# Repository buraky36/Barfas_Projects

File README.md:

# Barfas_Projects
IoT and Access Controller Projects

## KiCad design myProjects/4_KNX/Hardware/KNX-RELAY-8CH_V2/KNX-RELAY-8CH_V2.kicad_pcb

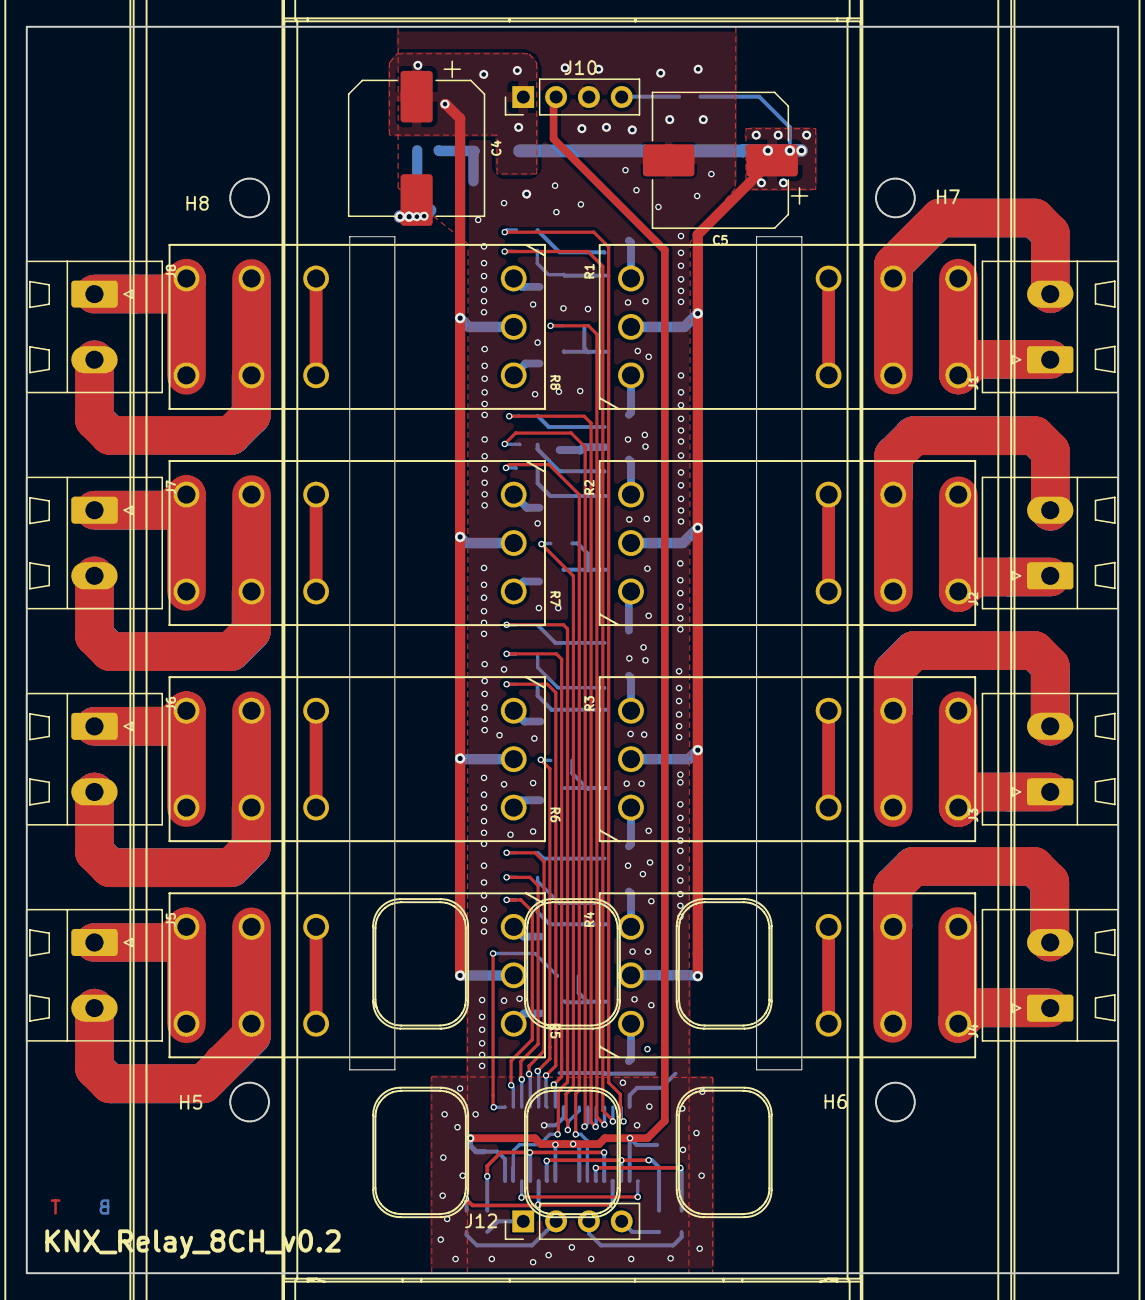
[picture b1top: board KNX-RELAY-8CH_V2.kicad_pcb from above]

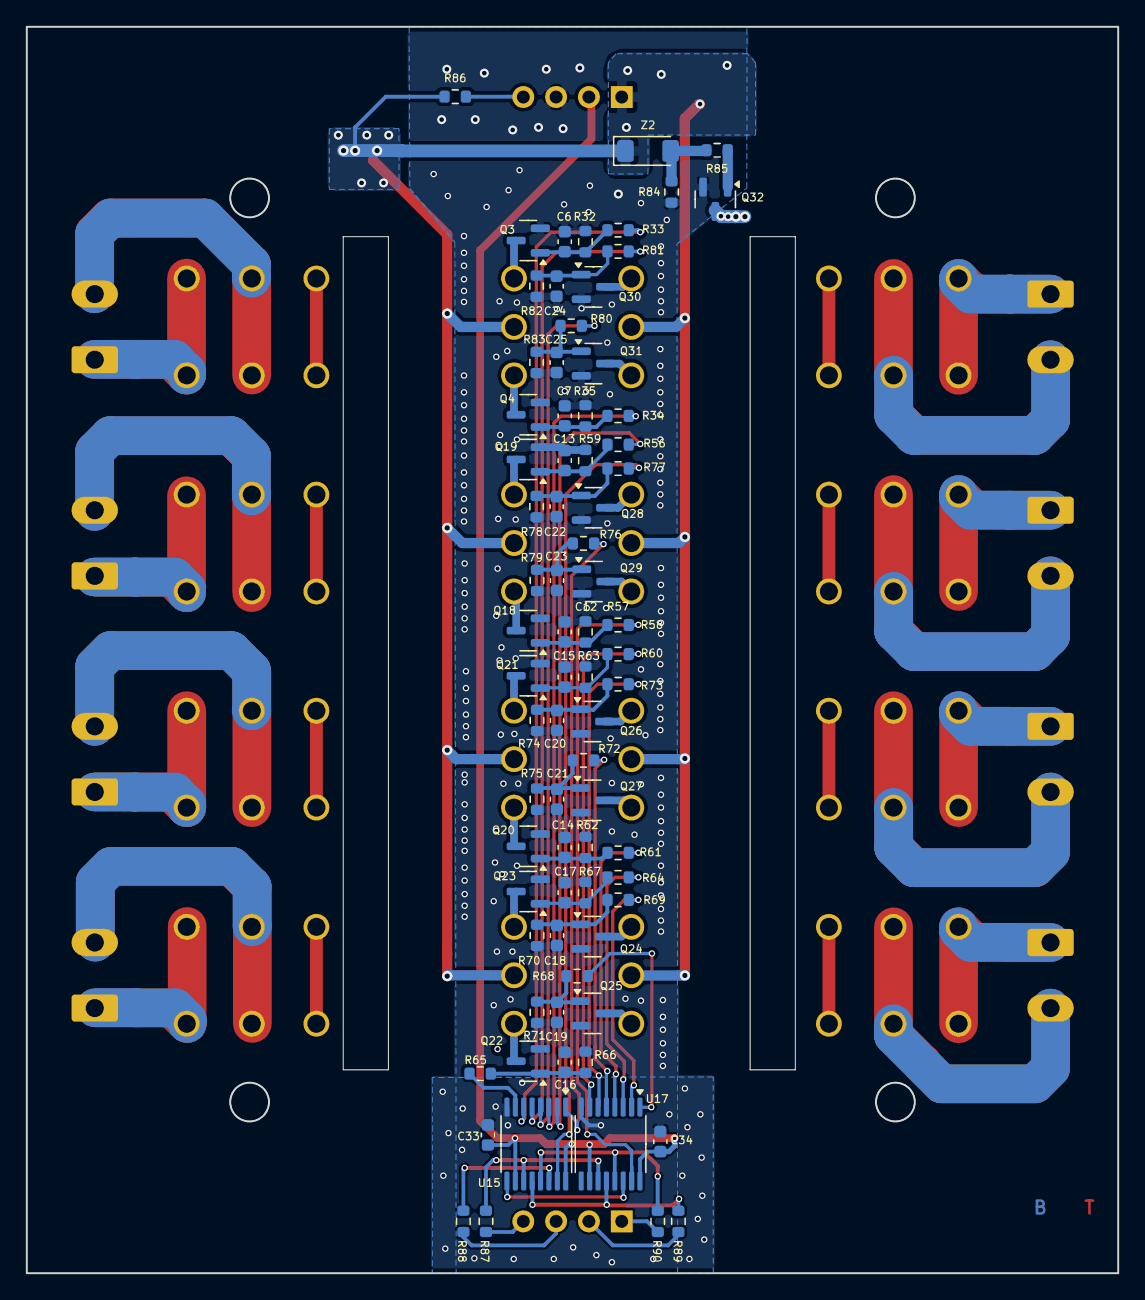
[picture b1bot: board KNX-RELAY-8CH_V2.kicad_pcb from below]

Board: 2 copper layers, 84.5 x 96.5 mm, 101 parts (77 on the bottom side), 80 nets.

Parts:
C4, C5: 1000uf/16V; CP_Elec_10x10
C6, C7, C12, C13, C14, C15, C16, C17, C18, C19, C20, C21, C22, C23, C24, C25: 100nF; C_0603_1608Metric
C33, C34: 100nF/50V; C_0603_1608Metric
H5, H6, H7, H8: MountingHole; MountingHole_3mm
J1, J2, J3, J4, J5, J6, J7, J8: DG129-5.08-02P-14-00AH; DG129-5.08-02P
J10, J12: Conn_01x04; PinHeader_1x04_P2.54mm_Vertical
Q3, Q4, Q18, Q19, Q20, Q21, Q22, Q23, Q24, Q25, Q26, Q27, Q28, Q29, Q30, Q31, Q32: 2N7002ET1G; SOT-23
R1, R2, R3, R4, R5, R6, R7, R8: RT314F12; RELAY9-500X1142_618
R32, R35, R58, R59, R62, R63, R66, R67, R70, R71, R74, R75, R78, R79, R82, R83, R84, R85: 10K; R_0603_1608Metric
R33, R34, R56, R57, R60, R61, R64, R65, R68, R69, R72, R73, R76, R77, R80, R81: 1K; R_0603_1608Metric
R86: 0R; R_0603_1608Metric
R87, R88, R89, R90: 33R; R_0603_1608Metric
U15, U17: 74HC595PW,118; TSSOP-16_4.4x5mm_P0.65mm
Z2: 6.8V; D_MiniMELF

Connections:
+3V3: C33.2, C34.2, J10.2, U15.10 (~SRCLR), U15.16 (VCC), U17.10 (~SRCLR), U17.16 (VCC)
+12V: C4.1, C5.1, J10.1, R1.A3, R2.A3, R3.A3, R4.A3, R5.A3, R6.A3, R7.A3, R8.A3, R86.1, Z2.1 (K)
/RELAYS/R1_COM: J1.2, R1.11
/RELAYS/R1_NO: J1.1, R1.14
/RELAYS/R2_COM: J2.2, R2.11
/RELAYS/R2_NO: J2.1, R2.14
/RELAYS/R3_COM: J3.2, R3.11
/RELAYS/R3_NO: J3.1, R3.14
/RELAYS/R4_COM: J4.2, R4.11
/RELAYS/R4_NO: J4.1, R4.14
/RELAYS/R5_COM: J5.2, R5.11
/RELAYS/R5_NO: J5.1, R5.14
/RELAYS/R6_COM: J6.2, R6.11
/RELAYS/R6_NO: J6.1, R6.14
/RELAYS/R7_COM: J7.2, R7.11
/RELAYS/R7_NO: J7.1, R7.14
/RELAYS/R8_COM: J8.2, R8.11
/RELAYS/R8_NO: J8.1, R8.14
/Shift register/ShiftRegCLK: R87.2, U15.11 (SRCLK), U17.11 (SRCLK)
/Shift register/ShiftRegDATA: R88.2, U15.14 (SER)
/Shift register/ShiftReg_Latch: R89.2, U15.12 (RCLK), U17.12 (RCLK)
/Shift register/Shift_~OE: R90.2, U15.13 (~OE), U17.13 (~OE)
GNDD: C5.2, C6.1, C7.1, C12.1, C13.1, C14.1, C15.1, C16.1, C17.1, C18.1, C19.1, C20.1, C21.1, C22.1, C23.1, C24.1, C25.1, C33.1, C34.1, J10.3, Q3.2 (S), Q4.2 (S), Q18.2 (S), Q19.2 (S), Q20.2 (S), Q21.2 (S), Q22.2 (S), Q23.2 (S), Q24.2 (S), Q25.2 (S), Q26.2 (S), Q27.2 (S), Q28.2 (S), Q29.2 (S), Q30.2 (S), Q31.2 (S), Q32.2 (S), R32.1, R35.1, R58.1, R59.1, R62.1, R63.1, R66.1, R67.1, R70.1, R71.1, R74.1, R75.1, R78.1, R79.1, R82.1, R83.1, R84.1, U15.8 (GND), U17.8 (GND)
unnamed: J12.1, R90.1
unnamed: J12.2, R89.1
unnamed: J12.3, R88.1
unnamed: J12.4, R87.1
unnamed: Q3.3 (D), R1.A2
unnamed: C6.2, Q3.1 (G), R32.2, R33.1
unnamed: Q4.3 (D), R1.A1
unnamed: C7.2, Q4.1 (G), R34.1, R35.2
unnamed: Q18.3 (D), R2.A1
unnamed: C12.2, Q18.1 (G), R57.1, R58.2
unnamed: Q19.3 (D), R2.A2
unnamed: C13.2, Q19.1 (G), R56.1, R59.2
unnamed: Q20.3 (D), R3.A1
unnamed: C14.2, Q20.1 (G), R61.1, R62.2
unnamed: Q21.3 (D), R3.A2
unnamed: C15.2, Q21.1 (G), R60.1, R63.2
unnamed: Q22.3 (D), R4.A1
unnamed: C16.2, Q22.1 (G), R65.1, R66.2
unnamed: Q23.3 (D), R4.A2
unnamed: C17.2, Q23.1 (G), R64.1, R67.2
unnamed: Q24.3 (D), R5.A1
unnamed: C18.2, Q24.1 (G), R69.1, R70.2
unnamed: Q25.3 (D), R5.A2
unnamed: C19.2, Q25.1 (G), R68.1, R71.2
unnamed: Q26.3 (D), R6.A1
unnamed: C20.2, Q26.1 (G), R73.1, R74.2
unnamed: Q27.3 (D), R6.A2
unnamed: C21.2, Q27.1 (G), R72.1, R75.2
unnamed: Q28.3 (D), R7.A1
unnamed: C22.2, Q28.1 (G), R77.1, R78.2
unnamed: Q29.3 (D), R7.A2
unnamed: C23.2, Q29.1 (G), R76.1, R79.2
unnamed: Q30.3 (D), R8.A1
unnamed: C24.2, Q30.1 (G), R81.1, R82.2
unnamed: Q31.3 (D), R8.A2
unnamed: C25.2, Q31.1 (G), R80.1, R83.2
unnamed: C4.2, Q32.3 (D)
unnamed: Q32.1 (G), R85.1
unnamed: U15.9 (QH'), U17.14 (SER)
unnamed: R84.2, R85.2, Z2.2 (A)
Relay_ADC: J10.4, R86.2
ShiftReg1_QA: R77.2, U15.15 (QA)
ShiftReg1_QB: R76.2, U15.1 (QB)
ShiftReg1_QC: R56.2, U15.2 (QC)
ShiftReg1_QD: R34.2, U15.3 (QD)
ShiftReg1_QE: R80.2, U15.4 (QE)
ShiftReg1_QF: R81.2, U15.5 (QF)
ShiftReg1_QG: R33.2, U15.6 (QG)
ShiftReg1_QH: R65.2, U15.7 (QH)
ShiftReg2_QA: R57.2, U17.15 (QA)
ShiftReg2_QB: R68.2, U17.1 (QB)
ShiftReg2_QC: R69.2, U17.2 (QC)
ShiftReg2_QD: R64.2, U17.3 (QD)
ShiftReg2_QE: R61.2, U17.4 (QE)
ShiftReg2_QF: R72.2, U17.5 (QF)
ShiftReg2_QG: R73.2, U17.6 (QG)
ShiftReg2_QH: R60.2, U17.7 (QH)

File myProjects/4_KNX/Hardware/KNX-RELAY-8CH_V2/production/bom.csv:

Designator,Footprint,Quantity,Value,LCSC Part #
"C12, C13, C14, C15, C16, C17, C18, C19, C20, C21, C22, C23, C24, C25, C6, C7",0603,16,100nF,
"C33, C34",0603,2,100nF/50V,
"C4, C5",CP_Elec_10x10,2,1000uf/16V,
"J1, J2, J3, J4, J5, J6, J7, J8",DG129-7.62-02P-14-00AH,8,DG129-7.62-02P-14-00AH,
"J10, J9",PinHeader_1x04_P2.54mm_Vertical,2,Conn_01x04,
"Q18, Q19, Q20, Q21, Q22, Q23, Q24, Q25, Q26, Q27, Q28, Q29, Q3, Q30, Q31, Q32, Q4",SOT-23,17,2N7002,
"R1, R2, R3, R4, R5, R6, R7, R8",RELAY9-500X1142_618,8,HF115F-L/12-HS3L2TF,
"R32, R35, R58, R59, R62, R63, R66, R67, R70, R71, R74, R75, R78, R79, R82, R83, R84, R85",0603,18,10K,
"R33, R34, R56, R57, R60, R61, R64, R65, R68, R69, R72, R73, R76, R77, R80, R81",0603,16,1K,
R86,0603,1,0R,
"R87, R88, R89, R90",0603,4,33R,
"U15, U17",TSSOP-16_4.4x5mm_P0.65mm,2,"74HC595PW,118",
Z2,D_MiniMELF,1,6.8V,

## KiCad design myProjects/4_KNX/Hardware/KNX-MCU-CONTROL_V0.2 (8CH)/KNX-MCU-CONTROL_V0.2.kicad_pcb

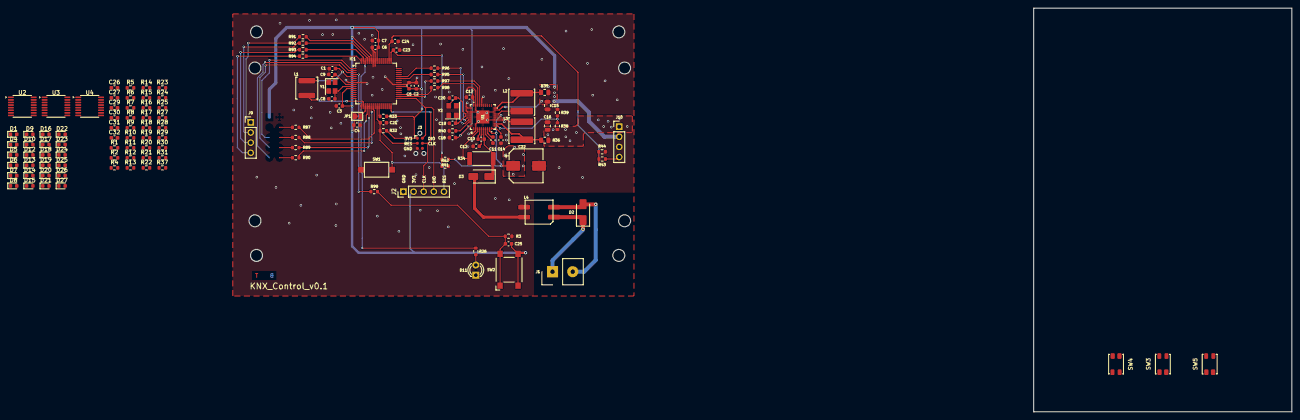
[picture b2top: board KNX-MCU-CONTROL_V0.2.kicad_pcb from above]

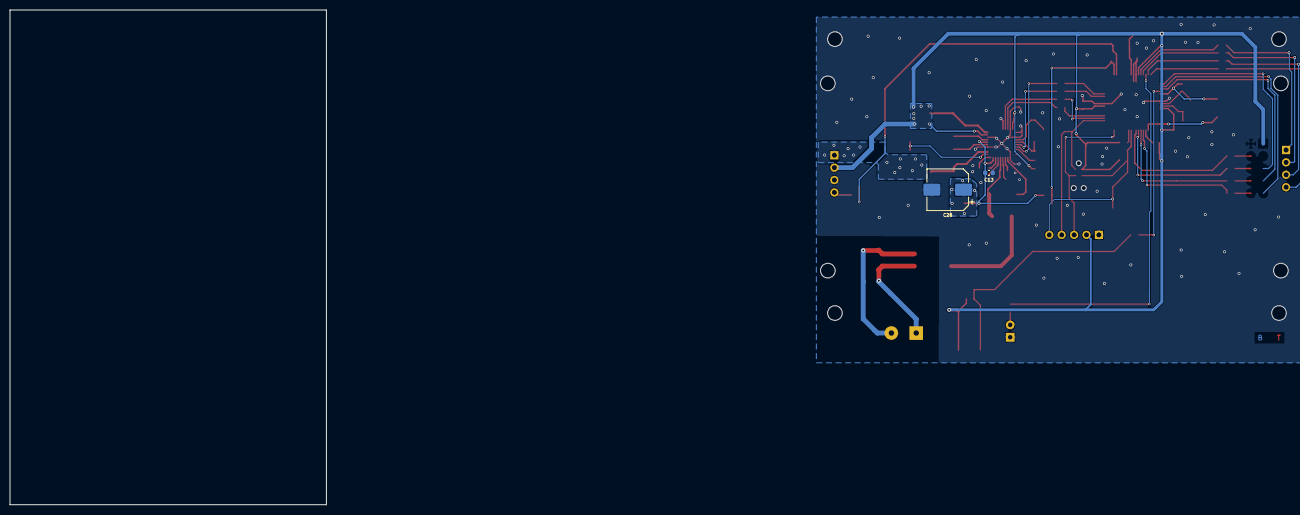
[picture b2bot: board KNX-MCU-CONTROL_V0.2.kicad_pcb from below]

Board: 2 copper layers, 64.8 x 101.3 mm, 146 parts (2 on the bottom side), 116 nets.

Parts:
C1: 4.7uF; C_0603_1608Metric
C2, C14: 1uF; C_0603_1608Metric
C3, C4, C5, C6, C12, C13, C17, C18, C21, C23, C24, C25, C26, C27, C29, C30, C31, C32: 100nF; C_0603_1608Metric
C7: 2.2uF; C_0603_1608Metric
C8, C9: 15pF; C_0603_1608Metric
C10: 47nF; C_0603_1608Metric
C11: 220nF; C_0603_1608Metric
C15, C16: 10uF; C_0805_2012Metric
C19, C20: 10pF; C_0603_1608Metric
C22: 100uF; CP_Elec_8x10
C28: 470uf/16V; CP_Elec_8x10
D1, D4, D5, D6, D7, D8, D9, D10, D12, D13, D14, D15, D16, D17, D18, D19, D20, D21, D22, D23, D24, D25, D26, D27: LED; LED_0603_1608Metric
D2: SMAJ40CA-HT; D_SMA
D3: SS28; D_SMA
D11: Led_Green; LED_D3.0mm
H1, H2, H3, H4, H5, H6, H7, H8: MountingHole; MountingHole_3mm
IC1: R7FA2L1AB3CFM; LQFP-64_10x10mm_P0.5mm
J1: L-KLS8-2170-13; Samtec_HPM-02-01-x-S_Straight_1x02_Pitch5.08mm
J2: Conn_01x05; PinHeader_1x05_P2.54mm_Vertical
J3: Conn_ARM_SWD_TagConnect_TC2030-NL; Tag-Connect_TC2030-IDC-NL_2x03_P1.27mm_Vertical
J9, J10: Conn_01x04; PinHeader_1x04_P2.54mm_Vertical
JP1: SolderJumper_2_Open; SolderJumper-2_P1.3mm_Open_TrianglePad1.0x1.5mm
L1: 4.7uH; L_APV_ANR5012
L2, L3: 220uH; L_APV_ANR6028
L4: 50474C; L_CommonMode_50474C_7.5x5.9mm
R1, R6, R7: 10k; R_0603_1608Metric
R2, R4, R5, R99: 330R; R_0603_1608Metric
R3, R32, R33, R39: 10K; R_0603_1608Metric
R8, R9, R10, R11, R12, R13, R14, R15, R16, R17, R18, R19, R20, R21, R22, R23, R24, R25, R27, R28, R29, R30, R31, R37: 1k; R_0603_1608Metric
R26: 1K; R_0603_1608Metric
R34: 27R; R_2512_6332Metric
R35, R36: 1R; R_0805_2012Metric
R38: 91K; R_0603_1608Metric
R40: 20k; R_0603_1608Metric
R41: 220k; R_0603_1608Metric
R42, R44: 27k; R_0603_1608Metric
R43: 100k; R_0603_1608Metric
R87, R88, R89, R90, R91, R92, R93, R94, R95, R96, R97, R98: 33R; R_0603_1608Metric
SW1: SW_Push; SW_SPST_CK_RS282G05A3
SW2: SW_Push; SW_SPST_Omron_B3FS-100xP
SW3, SW4, SW5: SW_MEC_5G; L-KLS7-TS3402-2.5
U1: NCN5130MNTWG; QFN40_485AU-01_ONS
U2, U3, U4: 74HC595PW,118; TSSOP-16_4.4x5mm_P0.65mm
Y1: 20Mhz; Crystal_SMD_SeikoEpson_FA238-4Pin_3.2x2.5mm
Y2: 16Mhz; Crystal_SMD_SeikoEpson_FA238V-4Pin_3.2x2.5mm

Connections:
3.3V: C26.1, C27.1, C29.1, SW3.3 (B), SW3.4 (B), SW4.3 (B), SW4.4 (B), SW5.3 (B), SW5.4 (B)
+3V3: C2.2, C3.2, C4.2, C5.2, C6.2, C7.2, C15.2, C17.2, C18.2, C25.2, C30.1, C31.1, C32.1, IC1.11 (VCC), IC1.39 (VCC), IC1.56 (AVCC0), IC1.59 (P010/VREFH0), J2.2, J3.1 (VCC), J10.2, JP1.1 (A), R32.2, R33.2, R35.2, SW2.2, U1.19 (VDD1), U1.30 (VDDD), U1.40 (VDDA), U2.10 (~SRCLR), U2.16 (VCC), U3.10 (~SRCLR), U3.16 (VCC), U4.10 (~SRCLR), U4.16 (VCC)
+12V: C16.2, J10.1, R36.2, R38.1, U1.13 (VDD2)
/CLK: IC1.32 (P300/SWCLK), J2.3, J3.4 (SWCLK)
/Connectors/RELAY_CAP_ADC: J10.4, R43.1
/Connectors/Relay_ShiftRegCLK: IC1.63 (P001), R94.1
/Connectors/Relay_ShiftRegDATA: IC1.64 (P000), R93.1
/Connectors/Relay_ShiftReg_Latch: IC1.61 (P003), R92.1
/Connectors/Relay_Shift_~OE: IC1.60 (P004), R91.1
/DIO: IC1.33 (P108/SWDIO), J2.4, J3.2 (SWDIO)
/MCU/P104: IC1.44 (P104), R96.2
/MCU/P105: IC1.43 (P105), R95.2
/MCU/P109: IC1.34 (P109), R97.2
/MCU/P110: IC1.35 (P110), R98.2
/MCU/P201/MD: IC1.26 (P201/MD), R33.1
/Transceiver for KNx/-A: D2.2 (A2), J1.2, L4.2
/Transceiver for KNx/A: D2.1 (A1), J1.1, L4.1
/Transceiver for KNx/RESETb: R96.1, U1.37 (RESETB)
/Transceiver for KNx/SAVEb: R95.1, U1.36 (SAVEB)
/Transceiver for KNx/SDI/RXD: R97.1, U1.27 (SDI/RXD)
/Transceiver for KNx/SDO/TXD: R98.1, U1.28 (SDO/TXD)
/Transceiver for KNx/VFILT: C13.2, C22.1, C28.1, R41.1, U1.9 (VFILT), U1.16 (VIN)
/UI_BUTTON_LED/ShiftRegCLK: IC1.22 (P206), U2.11 (SRCLK), U3.11 (SRCLK), U4.11 (SRCLK)
/UI_BUTTON_LED/ShiftRegDATA: IC1.23 (P205), U2.14 (SER)
/UI_BUTTON_LED/ShiftReg_Latch: IC1.21 (P207), U2.12 (RCLK), U3.12 (RCLK), U4.12 (RCLK)
/UI_BUTTON_LED/ShiftReg_~OE: IC1.20 (P208), U2.13 (~OE), U3.13 (~OE), U4.13 (~OE)
BTN_DOWN: IC1.3 (P402), R5.1
BTN_ENTER: IC1.2 (P401), R4.1
BTN_UP: IC1.1 (P400), R2.1
EXTAL: C8.1, IC1.10 (P212/EXTAL), Y1.2
GND: C30.2, C31.2, C32.2, D1.1 (K), D4.1 (K), D5.1 (K), D6.1 (K), D7.1 (K), D8.1 (K), D9.1 (K), D10.1 (K), D12.1 (K), D13.1 (K), D14.1 (K), D15.1 (K), D16.1 (K), D17.1 (K), D18.1 (K), D19.1 (K), D20.1 (K), D21.1 (K), D22.1 (K), D23.1 (K), D24.1 (K), D25.1 (K), D26.1 (K), D27.1 (K), R1.2, R6.2, R7.2, U2.8 (GND), U3.8 (GND), U4.8 (GND)
GNDD: C1.1, C2.1, C3.1, C4.1, C5.1, C6.1, C7.1, C8.2, C9.2, C12.1, C13.1, C14.1, C15.1, C16.1, C17.1, C18.1, C19.2, C20.2, C21.1, C22.2, C23.1, C24.1, C28.2, D11.1 (K), IC1.8 (VSS), IC1.17 (VSS_DCDC), IC1.40 (VSS), IC1.57 (AVSS0), IC1.58 (P011/VREFLO), J2.1, J3.5 (GND), J10.3, L4.3, R3.1, R39.2, R40.1, R42.2, R44.2, SW1.2, U1.1 (VSSA), U1.2 (VBUS2), U1.14 (VSS2), U1.18 (VSS1), U1.23 (MODE1), U1.24 (MODE2), U1.25 (TREQ), U1.26 (CSB/UC1), U1.29 (SCK/UC2), U1.31 (VSSD), U1.33 (XSEL), U1.41 (EPAD)
unnamed: C25.1, R3.2, R99.1, SW2.1
unnamed: C26.2, R1.1, R2.2, SW3.1 (A), SW3.2 (A)
unnamed: C27.2, R4.2, R6.1, SW4.1 (A), SW4.2 (A)
unnamed: C29.2, R5.2, R7.1, SW5.1 (A), SW5.2 (A)
unnamed: D1.2 (A), R8.2
unnamed: D3.2 (A), L4.4
unnamed: C10.2, D3.1 (K), R34.1, U1.6 (VBUS1)
unnamed: D4.2 (A), R9.2
unnamed: D5.2 (A), R10.2
unnamed: D6.2 (A), R11.2
unnamed: D7.2 (A), R12.2
unnamed: D8.2 (A), R13.2
unnamed: D9.2 (A), R14.2
unnamed: D10.2 (A), R15.2
unnamed: D11.2 (A), R26.2
unnamed: D12.2 (A), R16.2
unnamed: D13.2 (A), R17.2
unnamed: D14.2 (A), R18.2
unnamed: D15.2 (A), R19.2
unnamed: D16.2 (A), R20.2
unnamed: D17.2 (A), R21.2
unnamed: D18.2 (A), R22.2
unnamed: D19.2 (A), R23.2
unnamed: D20.2 (A), R24.2
unnamed: D21.2 (A), R25.2
unnamed: D22.2 (A), R27.2
unnamed: D23.2 (A), R28.2
unnamed: D24.2 (A), R29.2
unnamed: D25.2 (A), R30.2
unnamed: D26.2 (A), R31.2
unnamed: D27.2 (A), R37.2
unnamed: IC1.19 (VCC_DCDC), JP1.2 (B)
unnamed: C1.2, IC1.5 (VCL), L1.1
unnamed: IC1.18 (VLO), L1.2
unnamed: J9.1, R91.2
unnamed: J9.2, R92.2
unnamed: J9.3, R93.2
unnamed: J9.4, R94.2
unnamed: C12.2, U1.5 (CAV)
unnamed: C10.1, U1.4 (CCP)
unnamed: C11.2, U1.7 (CEQ1)
unnamed: C11.1, U1.8 (CEQ2)
unnamed: R40.2, U1.38 (FANIN)
unnamed: R34.2, U1.3 (TXO)
unnamed: C14.2, U1.10 (V20V)
unnamed: L2.2, R35.1, U1.20 (VDD1M)
unnamed: L3.2, R36.1, U1.12 (VDD2MC)
unnamed: R38.2, R39.1, U1.11 (VDD2MV)
unnamed: L2.1, U1.17 (VSW1)
unnamed: L3.1, U1.15 (VSW2)
unnamed: R8.1, U2.15 (QA)
unnamed: R9.1, U2.1 (QB)
unnamed: R10.1, U2.2 (QC)
unnamed: R11.1, U2.3 (QD)
unnamed: R12.1, U2.4 (QE)
unnamed: R13.1, U2.5 (QF)
unnamed: R14.1, U2.6 (QG)
unnamed: U2.9 (QH'), U3.14 (SER)
unnamed: R15.1, U2.7 (QH)
unnamed: R16.1, U3.15 (QA)
unnamed: R17.1, U3.1 (QB)
unnamed: R18.1, U3.2 (QC)
unnamed: R19.1, U3.3 (QD)
unnamed: R20.1, U3.4 (QE)
unnamed: R21.1, U3.5 (QF)
unnamed: R22.1, U3.6 (QG)
unnamed: U3.9 (QH'), U4.14 (SER)
unnamed: R23.1, U3.7 (QH)
unnamed: R24.1, U4.15 (QA)
unnamed: R25.1, U4.1 (QB)
unnamed: R27.1, U4.2 (QC)
unnamed: R28.1, U4.3 (QD)
unnamed: R29.1, U4.4 (QE)
unnamed: R30.1, U4.5 (QF)
unnamed: R31.1, U4.6 (QG)
unnamed: R37.1, U4.7 (QH)
RES: C21.2, IC1.25 (RES), J2.5, J3.3 (~RESET), R32.1, SW1.1
Relay_ADC: C24.2, IC1.50 (P501), R43.2, R44.1
User_BTN: IC1.4 (P403), R99.2
User_LED: IC1.62 (P002), R26.1
VFILT_ADC: C23.2, IC1.51 (P502), R41.2, R42.1
XTAL: C9.1, IC1.9 (P213/XTAL), Y1.1
XTAL1: C19.1, U1.35 (XTAL1), Y2.1
XTAL2: C20.1, U1.34 (XTAL2), Y2.3

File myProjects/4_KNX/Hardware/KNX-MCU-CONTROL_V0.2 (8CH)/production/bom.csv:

Designator,Footprint,Quantity,Value,LCSC Part #
C1,0603,1,4.7uF,
C10,0603,1,47nF,
C11,0603,1,220nF,
"C12, C13, C17, C18, C21, C23, C24, C25, C3, C4, C5, C6",0603,12,100nF,
"C14, C2",0603,2,1uF,
"C15, C16",0805,2,10uF,
"C19, C20",0603,2,10pF,
C22,CP_Elec_8x10,1,100uF,
C28,CP_Elec_8x10,1,470uf/16V,
C7,0603,1,2.2uF,
"C8, C9",0603,2,15pF,
D11,LED_D3.0mm,1,Led_Green,
D2,D_SMA,1,SMAJ40CA-HT,
D3,D_SMA,1,SS28,
IC1,LQFP-64_10x10mm_P0.5mm,1,R7FA2L1AB3CFM,
J1,Samtec_HPM-02-01-x-S_Straight_1x02_Pitch5.08mm,1,L-KLS8-2170-13,
"J10, J9",PinHeader_1x04_P2.54mm_Vertical,2,Conn_01x04,
J2,PinHeader_1x05_P2.54mm_Vertical,1,Conn_01x05,
J4,PinHeader_2x05_P2.54mm_Vertical,1,Conn_02x05_Counter_Clockwise,
L1,L_APV_ANR5012,1,4.7uH,
"L2, L3",L_APV_ANR6028,2,220uH,
L4,L_CommonMode_50474C_7.5x5.9mm,1,Choke_Wurth_WE-CNSW_744232090,
R26,0603,1,1K,
"R3, R32, R33, R39",0603,4,10K,
R34,2512,1,27R,
"R35, R36",0805,2,1R,
R38,0603,1,90K,
R40,0603,1,20k,
"R41, R43",0603,2,220k,
"R42, R44",0603,2,27k,
"R87, R88, R89, R90, R91, R92, R93, R94, R95, R96, R97, R98",0603,12,33R,
R99,0603,1,330R,
SW1,SW_SPST_CK_RS282G05A3,1,SW_Push,
SW2,SW_SPST_Omron_B3FS-100xP,1,SW_Push,
U1,QFN40_485AU-01_ONS,1,NCN5130MNTWG,
Y1,Crystal_SMD_SeikoEpson_FA238-4Pin_3.2x2.5mm,1,20Mhz,
Y2,Crystal_SMD_SeikoEpson_FA238V-4Pin_3.2x2.5mm,1,16Mhz,

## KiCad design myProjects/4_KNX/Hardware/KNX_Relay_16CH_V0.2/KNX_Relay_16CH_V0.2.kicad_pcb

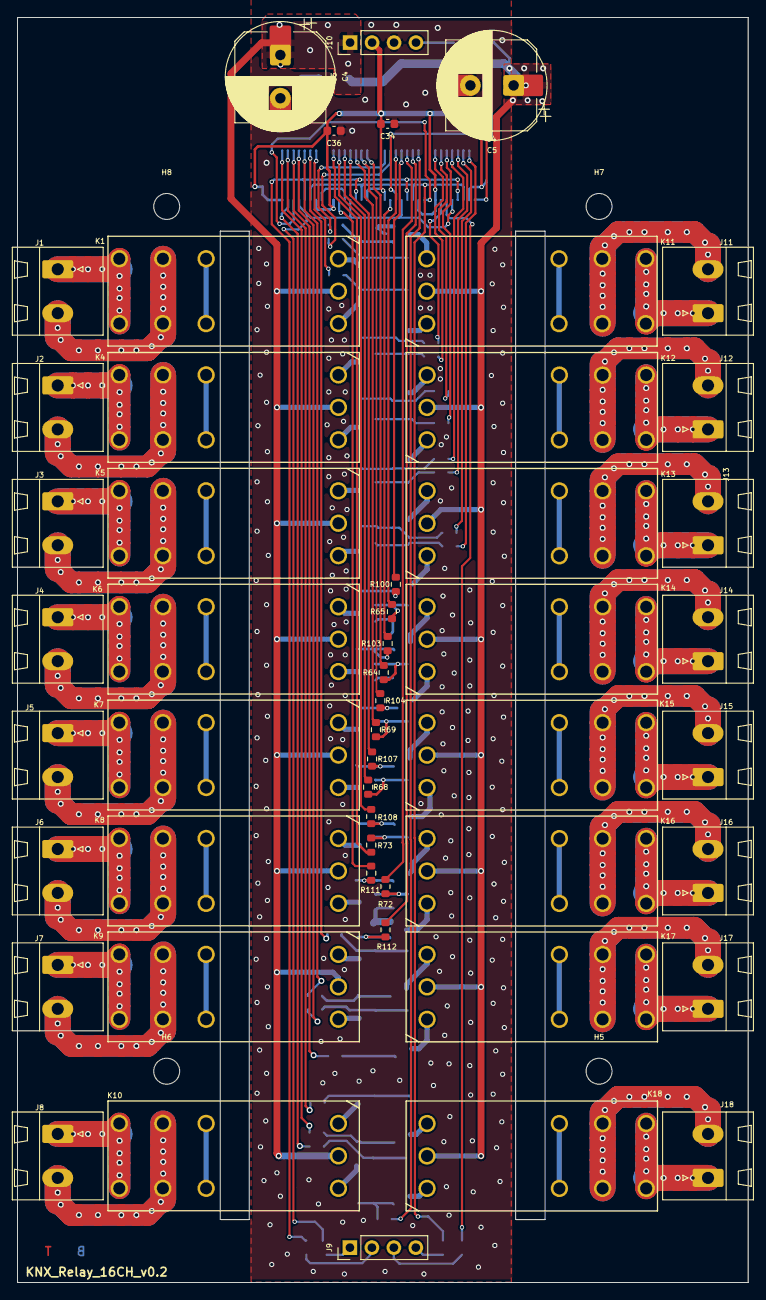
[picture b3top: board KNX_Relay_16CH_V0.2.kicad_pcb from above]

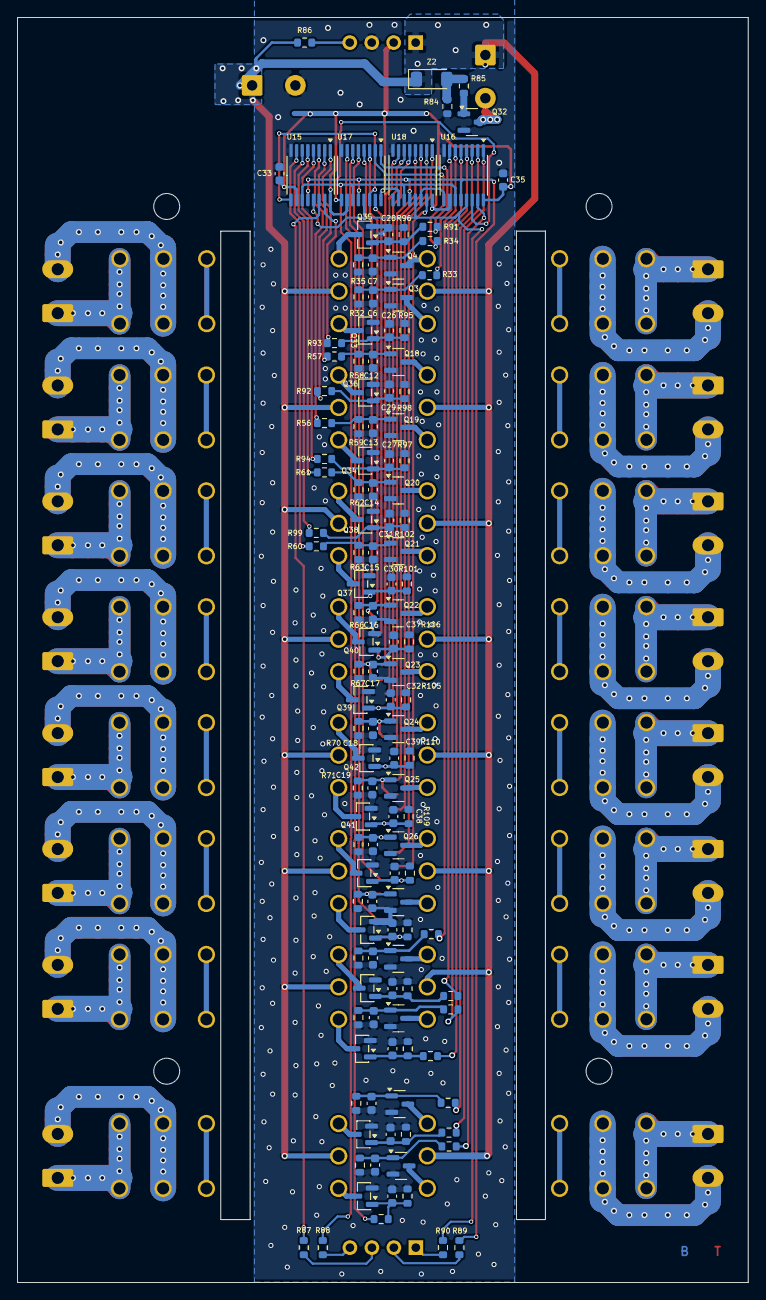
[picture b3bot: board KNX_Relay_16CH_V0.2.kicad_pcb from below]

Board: 2 copper layers, 84.5 x 146.3 mm, 187 parts (130 on the bottom side), 146 nets.

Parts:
C4, C5#2: 1500uf/35V; CP_Radial_D12.5mm_P5.00mm
C4#2, C5: 1000uf/16V; CP_Elec_10x10
C6, C7, C12, C13, C14, C15, C16, C17, C18, C19, C20, C21, C22, C23, C24, C25, C26, C27, C28, C29, C30, C31, C32, C33, C34, C35, C36, C37, C38, C39, C40, C41, C42, C43, C44, C45: 100nF; C_0603_1608Metric
H5, H6, H7, H8: MountingHole; MountingHole_3mm
J1, J2, J3, J4, J5, J6, J7, J8, J11, J12, J13, J14, J15, J16, J17, J18: DG129-5.08-02P-14-00AH; DG129-5.08-02P
J9, J10: Conn_01x04; PinHeader_1x04_P2.54mm_Vertical
K1, K4, K5, K6, K7, K8, K9, K10, K11, K12, K13, K14, K15, K16, K17, K18: RT314F12; RELAY9-500X1142_618
Q3, Q4, Q18, Q19, Q20, Q21, Q22, Q23, Q24, Q25, Q26, Q27, Q28, Q29, Q30, Q31, Q32, Q33, Q34, Q35, Q36, Q37, Q38, Q39, Q40, Q41, Q42, Q43, Q44, Q45, Q46, Q47, Q48: 2N7002ET1G; SOT-23
R32, R35, R58, R59, R62, R63, R66, R67, R70, R71, R74, R75, R78, R79, R82, R83, R84, R85, R95, R96, R97, R98, R101, R102, R105, R106, R109, R110, R113, R114, R117, R118, R121, R122: 10K; R_0603_1608Metric
R33, R34, R56, R57, R60, R61, R64, R65, R68, R69, R72, R73, R76, R77, R80, R81, R91, R92, R93, R94, R99, R100, R103, R104, R107, R108, R111, R112, R115, R116, R119, R120: 1K; R_0603_1608Metric
R86: 0R; R_0603_1608Metric
R87, R88, R89, R90: 33R; R_0603_1608Metric
U15, U16, U17, U18: 74HC595PW,118; TSSOP-16_4.4x5mm_P0.65mm
Z2: 6.8V; D_MiniMELF

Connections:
+3V3: C33.2, C34.2, C35.2, C36.2, J10.2, U15.10 (~SRCLR), U15.16 (VCC), U16.10 (~SRCLR), U16.16 (VCC), U17.10 (~SRCLR), U17.16 (VCC), U18.10 (~SRCLR), U18.16 (VCC)
+12V: C4.1, C4#2.1, C5.1, C5#2.1, J10.1, K1.A3, K4.A3, K5.A3, K6.A3, K7.A3, K8.A3, K9.A3, K10.A3, K11.A3, K12.A3, K13.A3, K14.A3, K15.A3, K16.A3, K17.A3, K18.A3, R86.1, Z2.1 (K)
/RELAYS/R1_A1: R34.2, U17.2 (QC)
/RELAYS/R1_A2: R33.2, U16.7 (QH)
/RELAYS/R1_COM: J1.2, K1.11
/RELAYS/R1_NO: J1.1, K1.14
/RELAYS/R2_COM: J2.2, K4.11
/RELAYS/R2_NO: J2.1, K4.14
/RELAYS/R3_COM: J3.2, K5.11
/RELAYS/R3_NO: J3.1, K5.14
/RELAYS/R4_A1: R65.2, U17.3 (QD)
/RELAYS/R4_A2: R64.2, U18.7 (QH)
/RELAYS/R4_COM: J4.2, K6.11
/RELAYS/R4_NO: J4.1, K6.14
/RELAYS/R5_A1: R69.2, U18.5 (QF)
/RELAYS/R5_A2: R68.2, U18.3 (QD)
/RELAYS/R5_COM: J5.2, K7.11
/RELAYS/R5_NO: J5.1, K7.14
/RELAYS/R6_A1: R73.2, U18.1 (QB)
/RELAYS/R6_A2: R72.2, U17.5 (QF)
/RELAYS/R6_COM: J6.2, K8.11
/RELAYS/R6_NO: J6.1, K8.14
/RELAYS/R7_A1: R77.2, U16.6 (QG)
/RELAYS/R7_A2: R76.2, U16.4 (QE)
/RELAYS/R7_COM: J7.2, K9.11
/RELAYS/R7_NO: J7.1, K9.14
/RELAYS/R8_A1: R81.2, U16.2 (QC)
/RELAYS/R8_A2: R80.2, U16.15 (QA)
/RELAYS/R8_COM: J8.2, K10.11
/RELAYS/R8_NO: J8.1, K10.14
/RELAYS/R9_A2: R91.2, U17.1 (QB)
/RELAYS/R9_COM: J11.2, K11.11
/RELAYS/R9_NO: J11.1, K11.14
/RELAYS/R10_COM: J12.2, K12.11
/RELAYS/R10_NO: J12.1, K12.14
/RELAYS/R11_A1: R100.2, U17.4 (QE)
/RELAYS/R11_COM: J13.2, K13.11
/RELAYS/R11_NO: J13.1, K13.14
/RELAYS/R12_A1: R104.2, U18.6 (QG)
/RELAYS/R12_A2: R103.2, U17.15 (QA)
/RELAYS/R12_COM: J14.2, K14.11
/RELAYS/R12_NO: J14.1, K14.14
/RELAYS/R13_A1: R108.2, U18.2 (QC)
/RELAYS/R13_A2: R107.2, U18.4 (QE)
/RELAYS/R13_COM: J15.2, K15.11
/RELAYS/R13_NO: J15.1, K15.14
/RELAYS/R14_A1: R112.2, U17.6 (QG)
/RELAYS/R14_A2: R111.2, U18.15 (QA)
/RELAYS/R14_COM: J16.2, K16.11
/RELAYS/R14_NO: J16.1, K16.14
/RELAYS/R15_A1: R116.2, U16.3 (QD)
/RELAYS/R15_A2: R115.2, U16.5 (QF)
/RELAYS/R15_COM: J17.2, K17.11
/RELAYS/R15_NO: J17.1, K17.14
/RELAYS/R16_A1: R120.2, U17.7 (QH)
/RELAYS/R16_A2: R119.2, U16.1 (QB)
/RELAYS/R16_COM: J18.2, K18.11
/RELAYS/R16_NO: J18.1, K18.14
/Shift register/ShiftRegCLK: R88.2, U15.11 (SRCLK), U16.11 (SRCLK), U17.11 (SRCLK), U18.11 (SRCLK)
/Shift register/ShiftRegDATA: R87.2, U15.14 (SER)
/Shift register/ShiftReg_Latch: R89.2, U15.12 (RCLK), U16.12 (RCLK), U17.12 (RCLK), U18.12 (RCLK)
/Shift register/Shift_~OE: R90.2, U15.13 (~OE), U16.13 (~OE), U17.13 (~OE), U18.13 (~OE)
GNDD: C4#2.2, C5#2.2, C6.1, C7.1, C12.1, C13.1, C14.1, C15.1, C16.1, C17.1, C18.1, C19.1, C20.1, C21.1, C22.1, C23.1, C24.1, C25.1, C26.1, C27.1, C28.1, C29.1, C30.1, C31.1, C32.1, C33.1, C34.1, C35.1, C36.1, C37.1, C38.1, C39.1, C40.1, C41.1, C42.1, C43.1, C44.1, C45.1, J10.3, Q3.2 (S), Q4.2 (S), Q18.2 (S), Q19.2 (S), Q20.2 (S), Q21.2 (S), Q22.2 (S), Q23.2 (S), Q24.2 (S), Q25.2 (S), Q26.2 (S), Q27.2 (S), Q28.2 (S), Q29.2 (S), Q30.2 (S), Q31.2 (S), Q32.2 (S), Q33.2 (S), Q34.2 (S), Q35.2 (S), Q36.2 (S), Q37.2 (S), Q38.2 (S), Q39.2 (S), Q40.2 (S), Q41.2 (S), Q42.2 (S), Q43.2 (S), Q44.2 (S), Q45.2 (S), Q46.2 (S), Q47.2 (S), Q48.2 (S), R32.1, R35.1, R58.1, R59.1, R62.1, R63.1, R66.1, R67.1, R70.1, R71.1, R74.1, R75.1, R78.1, R79.1, R82.1, R83.1, R84.1, R95.1, R96.1, R97.1, R98.1, R101.1, R102.1, R105.1, R106.1, R109.1, R110.1, R113.1, R114.1, R117.1, R118.1, R121.1, R122.1, U15.8 (GND), U16.8 (GND), U17.8 (GND), U18.8 (GND)
unnamed: J9.1, R90.1
unnamed: J9.2, R89.1
unnamed: J9.3, R87.1
unnamed: J9.4, R88.1
unnamed: K1.A2, Q3.3 (D)
unnamed: C6.2, Q3.1 (G), R32.2, R33.1
unnamed: K1.A1, Q4.3 (D)
unnamed: C7.2, Q4.1 (G), R34.1, R35.2
unnamed: K4.A1, Q18.3 (D)
unnamed: C12.2, Q18.1 (G), R57.1, R58.2
unnamed: K4.A2, Q19.3 (D)
unnamed: C13.2, Q19.1 (G), R56.1, R59.2
unnamed: K5.A1, Q20.3 (D)
unnamed: C14.2, Q20.1 (G), R61.1, R62.2
unnamed: K5.A2, Q21.3 (D)
unnamed: C15.2, Q21.1 (G), R60.1, R63.2
unnamed: K6.A1, Q22.3 (D)
unnamed: C16.2, Q22.1 (G), R65.1, R66.2
unnamed: K6.A2, Q23.3 (D)
unnamed: C17.2, Q23.1 (G), R64.1, R67.2
unnamed: K7.A1, Q24.3 (D)
unnamed: C18.2, Q24.1 (G), R69.1, R70.2
unnamed: K7.A2, Q25.3 (D)
unnamed: C19.2, Q25.1 (G), R68.1, R71.2
unnamed: K8.A1, Q26.3 (D)
unnamed: C20.2, Q26.1 (G), R73.1, R74.2
unnamed: K8.A2, Q27.3 (D)
unnamed: C21.2, Q27.1 (G), R72.1, R75.2
unnamed: K9.A1, Q28.3 (D)
unnamed: C22.2, Q28.1 (G), R77.1, R78.2
unnamed: K9.A2, Q29.3 (D)
unnamed: C23.2, Q29.1 (G), R76.1, R79.2
unnamed: K10.A1, Q30.3 (D)
unnamed: C24.2, Q30.1 (G), R81.1, R82.2
unnamed: K10.A2, Q31.3 (D)
unnamed: C25.2, Q31.1 (G), R80.1, R83.2
unnamed: C4.2, C5.2, Q32.3 (D)
unnamed: Q32.1 (G), R85.1
unnamed: K11.A1, Q33.3 (D)
unnamed: C26.2, Q33.1 (G), R93.1, R95.2
unnamed: K12.A1, Q34.3 (D)
unnamed: C27.2, Q34.1 (G), R94.1, R97.2
unnamed: K11.A2, Q35.3 (D)
unnamed: C28.2, Q35.1 (G), R91.1, R96.2
unnamed: K12.A2, Q36.3 (D)
unnamed: C29.2, Q36.1 (G), R92.1, R98.2
unnamed: K13.A1, Q37.3 (D)
unnamed: C30.2, Q37.1 (G), R100.1, R101.2
unnamed: K13.A2, Q38.3 (D)
unnamed: C31.2, Q38.1 (G), R99.1, R102.2
unnamed: K14.A1, Q39.3 (D)
unnamed: C32.2, Q39.1 (G), R104.1, R105.2
unnamed: K14.A2, Q40.3 (D)
unnamed: C37.2, Q40.1 (G), R103.1, R106.2
unnamed: K15.A1, Q41.3 (D)
unnamed: C38.2, Q41.1 (G), R108.1, R109.2
unnamed: K15.A2, Q42.3 (D)
unnamed: C39.2, Q42.1 (G), R107.1, R110.2
unnamed: K16.A1, Q43.3 (D)
unnamed: C40.2, Q43.1 (G), R112.1, R113.2
unnamed: K16.A2, Q44.3 (D)
unnamed: C41.2, Q44.1 (G), R111.1, R114.2
unnamed: K17.A1, Q45.3 (D)
unnamed: C42.2, Q45.1 (G), R116.1, R117.2
unnamed: K17.A2, Q46.3 (D)
unnamed: C43.2, Q46.1 (G), R115.1, R118.2
unnamed: K18.A1, Q47.3 (D)
unnamed: C44.2, Q47.1 (G), R120.1, R121.2
unnamed: K18.A2, Q48.3 (D)
unnamed: C45.2, Q48.1 (G), R119.1, R122.2
unnamed: U15.9 (QH'), U17.14 (SER)
unnamed: U16.9 (QH'), U18.14 (SER)
unnamed: U16.14 (SER), U17.9 (QH')
unnamed: R84.2, R85.2, Z2.2 (A)
Relay_ADC: J10.4, R86.2
ShiftReg1_QA: R93.2, U15.15 (QA)
ShiftReg1_QB: R57.2, U15.1 (QB)
ShiftReg1_QC: R92.2, U15.2 (QC)
ShiftReg1_QD: R56.2, U15.3 (QD)
ShiftReg1_QE: R94.2, U15.4 (QE)
ShiftReg1_QF: R61.2, U15.5 (QF)
ShiftReg1_QG: R99.2, U15.6 (QG)
ShiftReg1_QH: R60.2, U15.7 (QH)

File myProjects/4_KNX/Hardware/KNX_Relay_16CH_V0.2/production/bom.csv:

Designator,Footprint,Quantity,Value,LCSC Part #
"C12, C13, C14, C15, C16, C17, C18, C19, C20, C21, C22, C23, C24, C25, C26, C27, C28, C29, C30, C31, C32, C37, C38, C39, C40, C41, C42, C43, C44, C45, C6, C7",0603,32,100nF,
"C33, C34, C35, C36",0603,4,100nF/50V,
C4_2,CP_Radial_D12.5mm_P5.00mm,1,1500uf/35V,
"C4, C5",CP_Elec_10x10,2,1000uf/16V,
C5_2,CP_Radial_D12.5mm_P5.00mm,1,1500/35V,
"J1, J11, J12, J13, J14, J15, J16, J17, J18, J2, J3, J4, J5, J6, J7, J8",DG129-7.62-02P-14-00AH,16,DG129-7.62-02P-14-00AH,
"J10, J9",PinHeader_1x04_P2.54mm_Vertical,2,Conn_01x04,
"K1, K10, K11, K12, K13, K14, K15, K16, K17, K18, K4, K5, K6, K7, K8, K9",RELAY9-500X1142_618,16,HF115F-L/12-HS3L2TF,
"Q18, Q19, Q20, Q21, Q22, Q23, Q24, Q25, Q26, Q27, Q28, Q29, Q3, Q30, Q31, Q32, Q33, Q34, Q35, Q36, Q37, Q38, Q39, Q4, Q40, Q41, Q42, Q43, Q44, Q45, Q46, Q47, Q48",SOT-23,33,2N7002,
"R100, R103, R104, R107, R108, R111, R112, R115, R116, R119, R120, R33, R34, R56, R57, R60, R61, R64, R65, R68, R69, R72, R73, R76, R77, R80, R81, R91, R92, R93, R94, R99",0603,32,1K,
"R101, R102, R105, R106, R109, R110, R113, R114, R117, R118, R121, R122, R32, R35, R58, R59, R62, R63, R66, R67, R70, R71, R74, R75, R78, R79, R82, R83, R84, R85, R95, R96, R97, R98",0603,34,10K,
R86,0603,1,0R,
"R87, R88, R89, R90",0603,4,33R,
"U15, U16, U17, U18",TSSOP-16_4.4x5mm_P0.65mm,4,"74HC595PW,118",
Z2,D_MiniMELF,1,6.8V,

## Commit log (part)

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2026-05-15 şaptop
    first init
2026-05-15 pc
    first init
2026-05-15 pc
    init
2026-06-02 burak PC
    init
2026-06-06 burak laptop
    init
2026-06-09 laptop
    init
2026-06-14 feat: add firmware version v1.0.0 to boot log
2026-06-14 PC
    İNİT
2026-06-20 Working state before Wiegand array upgrade
2026-06-20 init
    Wiegand çalışması sorunları çözüldü. 26bit ve 34bit çalışması düzeltilmiştir.
2026-06-21 init
    init
2026-06-22 init
    Wi-Fi bağlantısı, MQTT sunucu ve node cihaz haberleşme testleri başarılı. OTA başarılı.
2026-06-27 init
    init.
    Online MQTT entegrasyonu tamamladım.
